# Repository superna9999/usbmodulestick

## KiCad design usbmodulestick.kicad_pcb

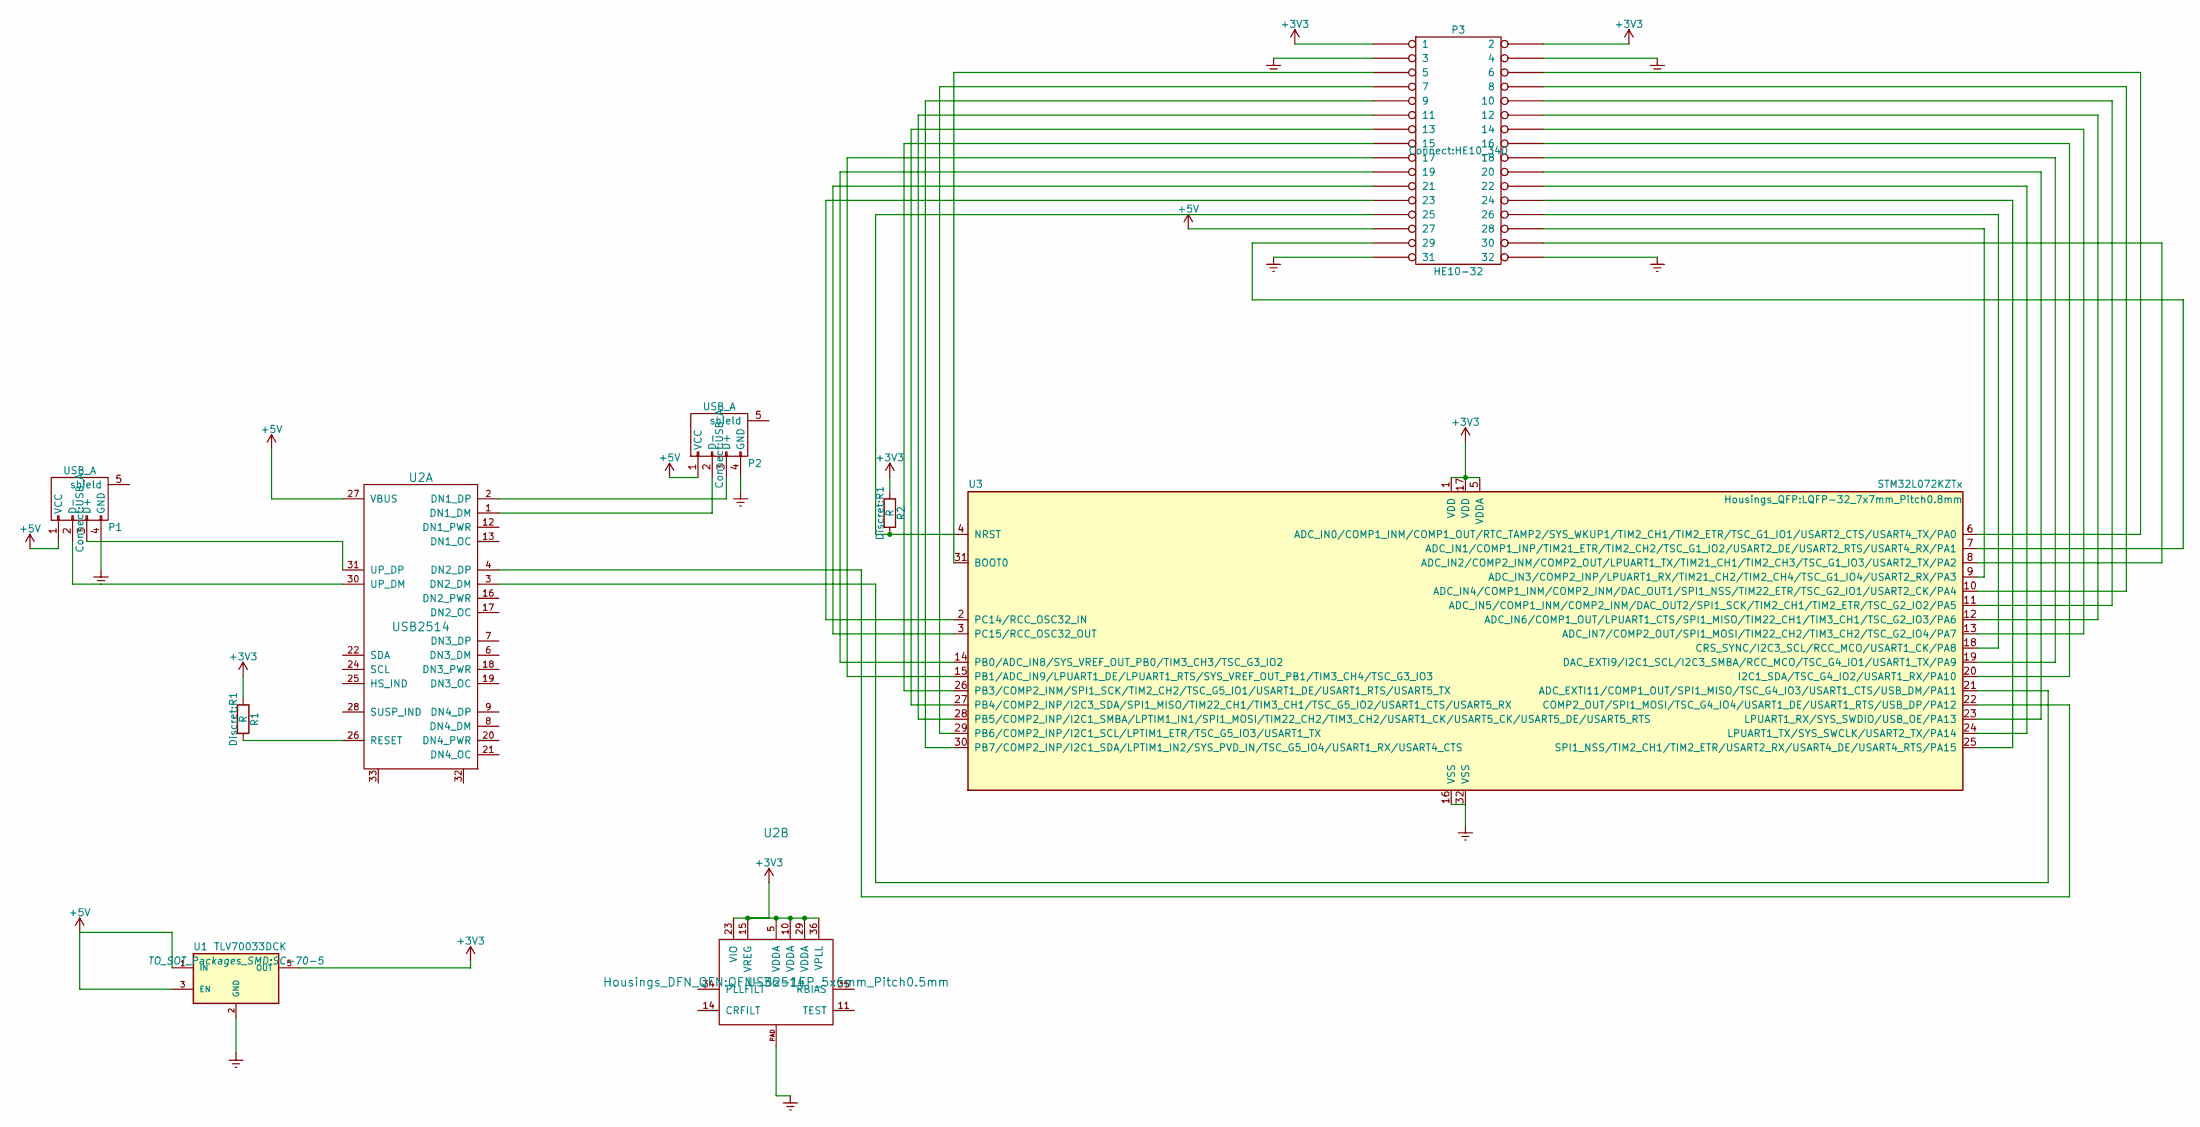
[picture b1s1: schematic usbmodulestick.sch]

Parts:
P1, P2: USB_A
P3: HE10-32; HE10_34D
R1, R2: R; R1
U1: TLV70033DCK; SC-70-5
U2: USB2514; QFN-36-1EP_5x6mm_Pitch0.5mm
U3: STM32L072KZTx; LQFP-32_7x7mm_Pitch0.8mm

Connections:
+3V3: P3.1, P3.2, R1.1, R2.1, U1.5 (OUT), U2.5 (VDDA), U2.10 (VDDA), U2.15 (VREG), U2.23 (VIO), U2.29 (VDDA), U2.36 (VPLL), U3.1 (VDD), U3.5 (VDDA), U3.17 (VDD)
+5V: P1.1 (VCC), P2.1 (VCC), P3.27, U1.1 (IN), U1.3 (EN), U2.27 (VBUS)
Earth: P1.4 (GND), P2.4 (GND), P3.3, P3.4, P3.31, P3.32, U1.2 (GND), U2.PAD, U3.16 (VSS), U3.32 (VSS)
unnamed: P1.2 (D-), U2.30 (UP_DM)
unnamed: P1.3 (D+), U2.31 (UP_DP)
unnamed: P2.2 (D-), U2.1 (DN1_DM)
unnamed: P2.3 (D+), U2.2 (DN1_DP)
unnamed: P3.5, U3.31 (BOOT0)
unnamed: P3.6, U3.6 (ADC_IN0/COMP1_INM/COMP1_OUT/RTC_TAMP2/S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)
unnamed: P3.7, U3.29 (PB6/COMP2_INP/I2C1_SCL/LPTIM1_ETR/TSC_G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)
unnamed: P3.8, U3.10 (ADC_IN4/COMP1_INM/COMP2_INM/DAC_OUT1/SP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)
unnamed: P3.9, U3.30 (PB7/COMP2_INP/I2C1_SDA/LPTIM1_IN2/SYS_P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)
unnamed: P3.10, U3.11 (ADC_IN5/COMP1_INM/COMP2_INM/DAC_OUT2/SP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)
unnamed: P3.11, U3.28 (PB5/COMP2_INP/I2C1_SMBA/LPTIM1_IN1/SPI1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)
unnamed: P3.12, U3.12 (ADC_IN6/COMP1_OUT/LPUART1_CTS/SPI1_MISO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)
unnamed: P3.13, U3.27 (PB4/COMP2_INP/I2C3_SDA/SPI1_MISO/TIM22_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)
unnamed: P3.14, U3.13 (ADC_IN7/COMP2_OUT/SPI1_MOSI/TIM22_CH2/T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)
unnamed: P3.15, U3.26 (PB3/COMP2_INM/SPI1_SCK/TIM2_CH2/TSC_G5_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)
unnamed: P3.16, U3.20 (I2C1_SDA/TSC_G4_IO2/USART1_RX/PA10)
unnamed: P3.17, U3.15 (PB1/ADC_IN9/LPUART1_DE/LPUART1_RTS/SYS_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)
unnamed: P3.18, U3.19 (DAC_EXTI9/I2C1_SCL/I2C3_SMBA/RCC_MCO/TS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)
unnamed: P3.19, U3.14 (PB0/ADC_IN8/SYS_VREF_OUT_PB0/TIM3_CH3/T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)
unnamed: P3.20, U3.23 (LPUART1_RX/SYS_SWDIO/USB_OE/PA13)
unnamed: P3.21, U3.3 (PC15/RCC_OSC32_OUT)
unnamed: P3.22, U3.24 (LPUART1_TX/SYS_SWCLK/USART2_TX/PA14)
unnamed: P3.23, U3.2 (PC14/RCC_OSC32_IN)
unnamed: P3.24, U3.25 (SPI1_NSS/TIM2_CH1/TIM2_ETR/USART2_RX/US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)
unnamed: P3.25, R2.2, U3.4 (NRST)
unnamed: P3.26, U3.18 (CRS_SYNC/I2C3_SCL/RCC_MCO/USART1_CK/PA8)
unnamed: P3.28, U3.9 (ADC_IN3/COMP2_INP/LPUART1_RX/TIM21_CH2/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)
unnamed: P3.29, U3.7 (ADC_IN1/COMP1_INP/TIM21_ETR/TIM2_CH2/TS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)
unnamed: P3.30, U3.8 (ADC_IN2/COMP2_INM/COMP2_OUT/LPUART1_TX/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)
unnamed: R1.2, U2.26 (RESET)
unnamed: U2.3 (DN2_DM), U3.21 (ADC_EXTI11/COMP1_OUT/SPI1_MISO/TSC_G4_I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)
unnamed: U2.4 (DN2_DP), U3.22 (COMP2_OUT/SPI1_MOSI/TSC_G4_IO4/USART1_D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)

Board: 2 copper layers, 8 parts (0 on the bottom side), 35 nets, no tracks yet.

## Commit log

2022-08-31 Import
